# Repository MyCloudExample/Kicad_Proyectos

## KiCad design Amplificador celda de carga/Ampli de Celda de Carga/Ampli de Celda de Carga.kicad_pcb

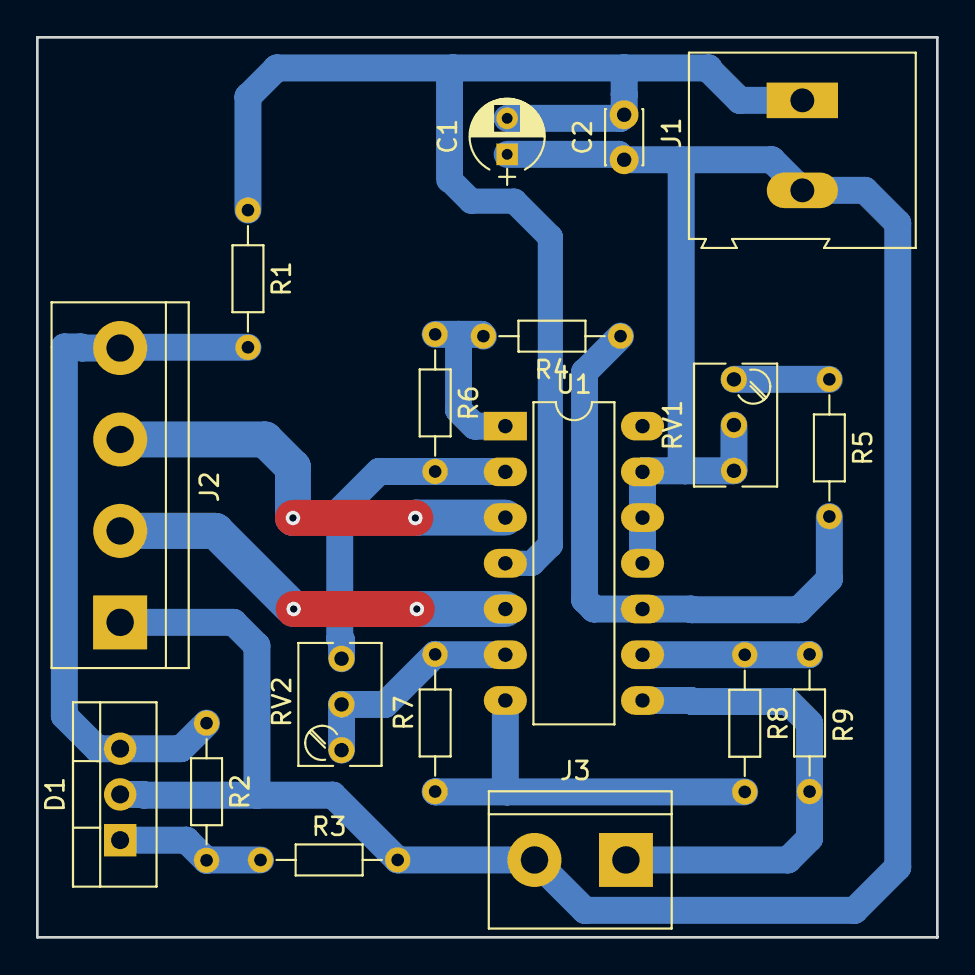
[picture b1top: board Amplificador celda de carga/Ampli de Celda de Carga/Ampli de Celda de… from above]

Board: 2 copper layers, 50.0 x 50.0 mm, 18 parts (0 on the bottom side), 14 nets.

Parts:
C1: 100uF; CP_Radial_D4.0mm_P2.00mm
C2: 0,1uF; C_Disc_D3.0mm_W2.0mm_P2.50mm
D1: TL431LP; TO-220-3_Vertical
J1: 12V GND; TerminalBlock_Altech_AK300-2_P5.00mm
J2: CargaBalanceada; TerminalBlock_bornier-4_P5.08mm
J3: Salida; TerminalBlock_bornier-2_P5.08mm
R1: 4k7; R_Axial_DIN0204_L3.6mm_D1.6mm_P7.62mm_Horizontal
R2, R3: 2k2; R_Axial_DIN0204_L3.6mm_D1.6mm_P7.62mm_Horizontal
R4, R6, R7, R8, R9: 10k; R_Axial_DIN0204_L3.6mm_D1.6mm_P7.62mm_Horizontal
R5: 8k2; R_Axial_DIN0204_L3.6mm_D1.6mm_P7.62mm_Horizontal
RV1: 2k; Potentiometer_Trimmer_Bourns_3266Y
RV2: 10k; Potentiometer_Trimmer_Bourns_3266Y
U1: LM324; DIP-14_W7.62mm_LongPads

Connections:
/5V: D1.3, J2.4, R1.2, R2.1
GNDREF: C1.1, C2.1, D1.2, J1.2, J2.1, J3.2, R3.2, RV1.2, RV1.3, U1.11, U1.12, U1.13
unnamed: D1.1, R2.2, R3.1
unnamed: J2.2, U1.5
unnamed: J2.3, U1.3
unnamed: J3.1, R9.1, U1.8
unnamed: R4.1, R5.2, U1.10
unnamed: R4.2, R6.1, U1.1
unnamed: R5.1, RV1.1
unnamed: R6.2, RV2.3, U1.2
unnamed: R7.1, R8.2, U1.7
unnamed: R7.2, RV2.1, RV2.2, U1.6
unnamed: R8.1, R9.2, U1.9
VDD: C1.2, C2.2, J1.1, R1.1, U1.4

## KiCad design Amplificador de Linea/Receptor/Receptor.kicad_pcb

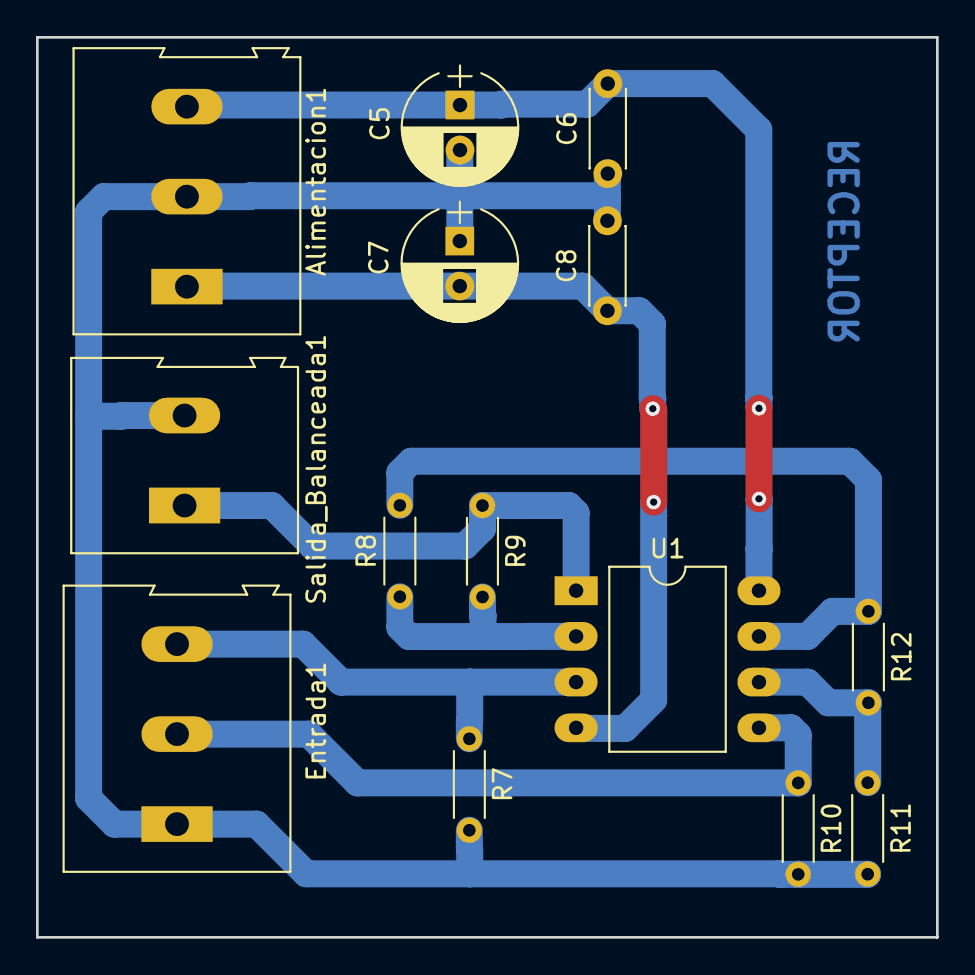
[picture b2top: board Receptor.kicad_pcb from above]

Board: 2 copper layers, 50.0 x 50.0 mm, 14 parts (0 on the bottom side), 9 nets.

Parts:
Alimentacion1: -12V 0V +12V; TerminalBlock_Altech_AK300-3_P5.00mm
C5, C7: 100uF; CP_Radial_D6.3mm_P2.50mm
C6, C8: 0,1uF; C_Disc_D4.3mm_W1.9mm_P5.00mm
Entrada1: TerminalBlock_Altech_AK300-3_P5.00mm
R7, R8, R9, R10, R11, R12: 10k; R_Axial_DIN0204_L3.6mm_D1.6mm_P5.08mm_Horizontal
Salida_Balanceada1: TerminalBlock_Altech_AK300-2_P5.00mm
U1: RC4558; DIP-8_W10.16mm_LongPads

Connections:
GNDREF: Alimentacion1.2, C5.2, C6.1, C7.1, C8.2, Entrada1.1, R7.2, R10.2, R11.2, Salida_Balanceada1.2
unnamed: Entrada1.2, R10.1, U1.5
unnamed: Entrada1.3, R7.1, U1.3
unnamed: R8.1, R9.2, U1.2
unnamed: R9.1, Salida_Balanceada1.1, U1.1
unnamed: R11.1, R12.2, U1.6
unnamed: R8.2, R12.1, U1.7
VDD: Alimentacion1.3, C5.1, C6.2, U1.8
VSS: Alimentacion1.1, C7.2, C8.1, U1.4

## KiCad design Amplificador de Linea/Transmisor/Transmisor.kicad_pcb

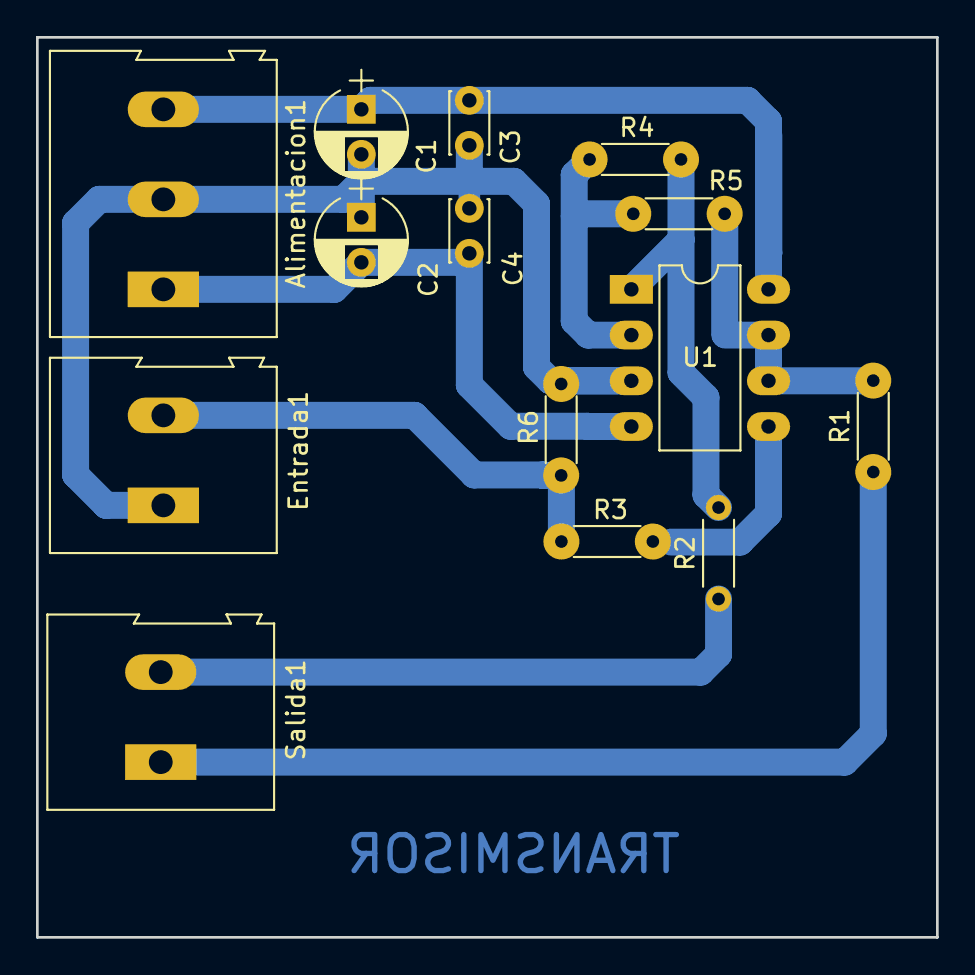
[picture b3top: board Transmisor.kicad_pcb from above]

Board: 2 copper layers, 50.0 x 50.0 mm, 14 parts (0 on the bottom side), 10 nets.

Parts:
Alimentacion1: -12V 0V +12V; TerminalBlock_Altech_AK300-3_P5.00mm
C1, C2: 100uF; CP_Radial_D5.0mm_P2.50mm
C3, C4: 0,1uF; C_Disc_D3.4mm_W2.1mm_P2.50mm
Entrada1: TerminalBlock_Altech_AK300-2_P5.00mm
R1, R2: 100; R_Axial_DIN0204_L3.6mm_D1.6mm_P5.08mm_Horizontal
R3: 1k; R_Axial_DIN0204_L3.6mm_D1.6mm_P5.08mm_Horizontal
R4, R5, R6: 10k; R_Axial_DIN0204_L3.6mm_D1.6mm_P5.08mm_Horizontal
Salida1: TerminalBlock_Altech_AK300-2_P5.00mm
U1: RC4558; DIP-8_W7.62mm_LongPads

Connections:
GNDREF: Alimentacion1.2, C1.2, C2.1, C3.1, C4.2, Entrada1.1, R6.1, U1.3
unnamed: Entrada1.2, R3.2, R6.2
unnamed: R1.1, Salida1.1
unnamed: R1.2, R4.2, U1.6, U1.7
unnamed: R2.1, Salida1.2
unnamed: R2.2, R5.1, U1.1
unnamed: R3.1, U1.5
unnamed: R4.1, R5.2, U1.2
VDD: Alimentacion1.3, C1.1, C3.2, U1.8
VSS: Alimentacion1.1, C2.2, C4.1, U1.4

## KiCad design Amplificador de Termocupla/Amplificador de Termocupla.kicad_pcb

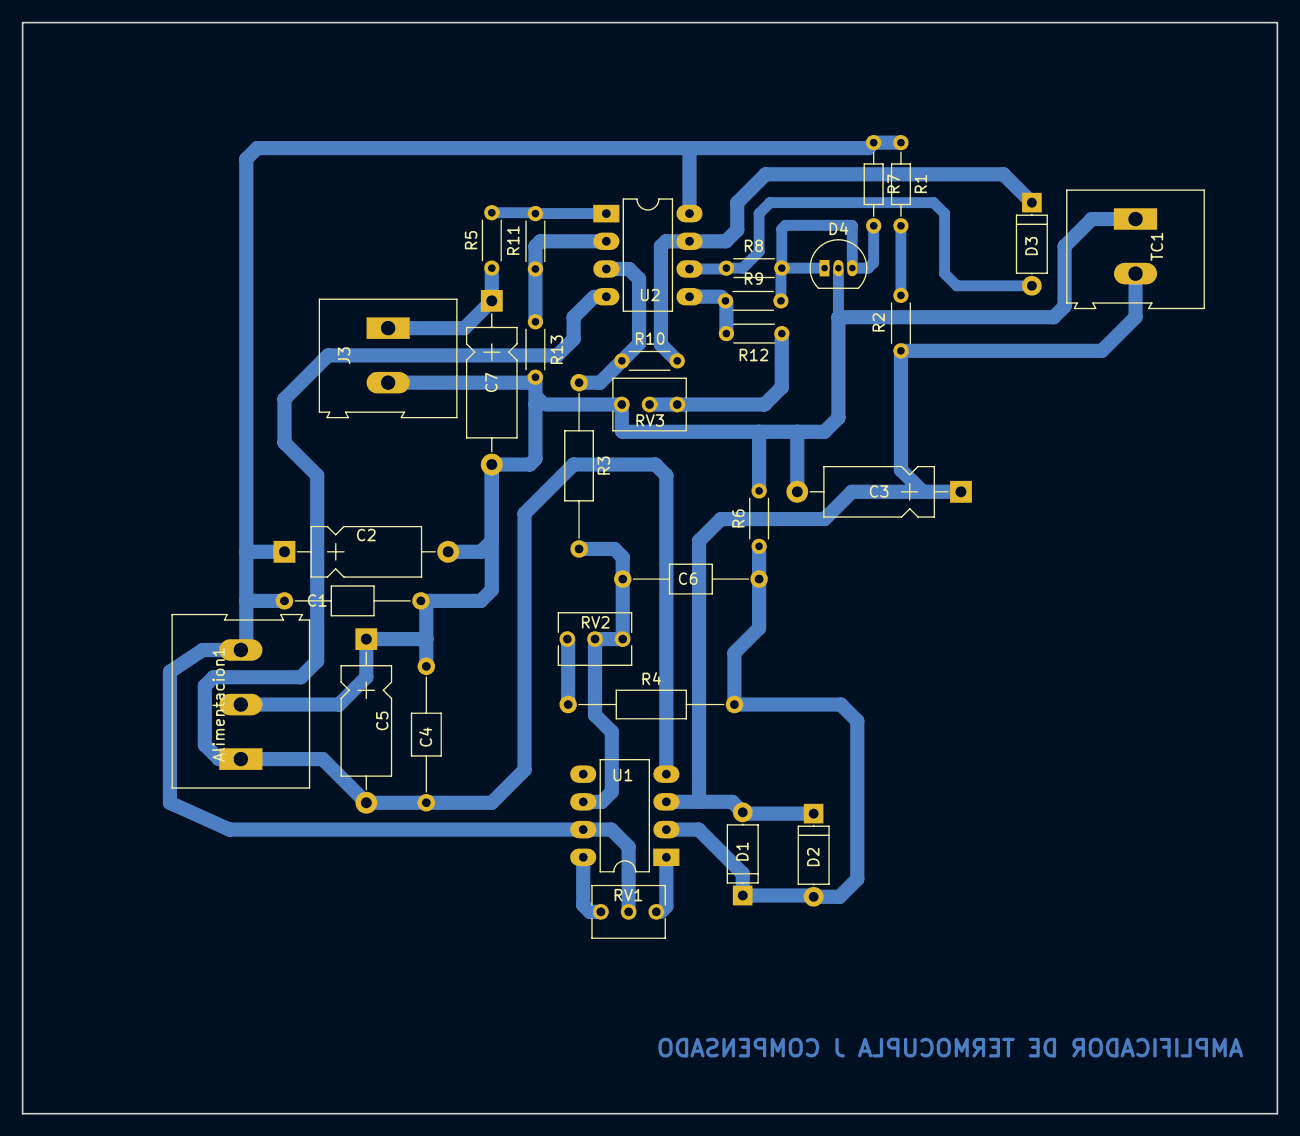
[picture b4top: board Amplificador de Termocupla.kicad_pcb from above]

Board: 2 copper layers, 115.0 x 100.0 mm, 32 parts (0 on the bottom side), 19 nets.

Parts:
Alimentacion1: -15 GND +15; TerminalBlock_Altech_AK300-3_P5.00mm
C1, C4, C6: 0.1uF; C_Axial_L3.8mm_D2.6mm_P12.50mm_Horizontal
C2, C5: 100uF; CP_Axial_L10.0mm_D4.5mm_P15.00mm_Horizontal
C3, C7: 1uF; CP_Axial_L10.0mm_D4.5mm_P15.00mm_Horizontal
D1, D2, D3: D_A-405_P7.62mm_Horizontal
D4: TL431LP; TO-92_Inline_Narrow_Oval
J3: Sensor_V_Out; TerminalBlock_Altech_AK300-2_P5.00mm
R1: 1M; R_Axial_DIN0204_L3.6mm_D1.6mm_P7.62mm_Horizontal
R2, R5, R6: 1K; R_Axial_DIN0204_L3.6mm_D1.6mm_P5.08mm_Horizontal
R3: 10K; R_Axial_DIN0207_L6.3mm_D2.5mm_P15.24mm_Horizontal
R4: 39K; R_Axial_DIN0207_L6.3mm_D2.5mm_P15.24mm_Horizontal
R7: R; R_Axial_DIN0204_L3.6mm_D1.6mm_P7.62mm_Horizontal
R8, R9: 18K; R_Axial_DIN0204_L3.6mm_D1.6mm_P5.08mm_Horizontal
R10, R13: 10K; R_Axial_DIN0204_L3.6mm_D1.6mm_P5.08mm_Horizontal
R11: 75K; R_Axial_DIN0204_L3.6mm_D1.6mm_P5.08mm_Horizontal
R12: 4K7; R_Axial_DIN0204_L3.6mm_D1.6mm_P5.08mm_Horizontal
RV1: 20K; Potentiometer_Trimmer_Vishay_T73XW_Vertical
RV2: 10K; Potentiometer_Trimmer_Vishay_T73XW_Vertical
RV3: 1K; Potentiometer_Trimmer_Vishay_T73XW_Vertical
TC1: Termocupla J; TerminalBlock_Altech_AK300-2_P5.00mm
U1: OP07; DIP-8_W7.62mm_LongPads
U2: LM358; DIP-8_W7.62mm_LongPads

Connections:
Earth: Alimentacion1.2, C1.2, C2.2, C3.2, C4.1, C5.1, C7.2, D4.2, J3.2, R6.2, R13.1, RV3.3, TC1.1
unnamed: C3.1, D1.2, D2.1, R2.2, TC1.2, U1.3
unnamed: C6.1, R3.2, RV2.1, RV2.2, U1.6
unnamed: C6.2, D1.1, D2.2, R4.2, R6.1, U1.2
unnamed: C7.1, J3.1, R5.1
unnamed: D3.1, R10.1, U2.7
unnamed: D3.2, R8.1, U2.6
unnamed: D4.1, D4.3, R7.2, R8.2, R9.1
unnamed: R1.2, R2.1
unnamed: R4.1, RV2.3
unnamed: R3.1, R10.2, U2.3
unnamed: R5.2, R11.1, U2.1
unnamed: R11.2, R13.2, U2.2
unnamed: R9.2, R12.1, U2.5
unnamed: R12.2, RV3.1, RV3.2
unnamed: RV1.1, U1.8
unnamed: RV1.3, U1.1
VDD: Alimentacion1.3, C1.1, C2.1, R1.1, R7.1, RV1.2, U1.7, U2.8
VEE: Alimentacion1.1, C4.2, C5.2, U1.4, U2.4

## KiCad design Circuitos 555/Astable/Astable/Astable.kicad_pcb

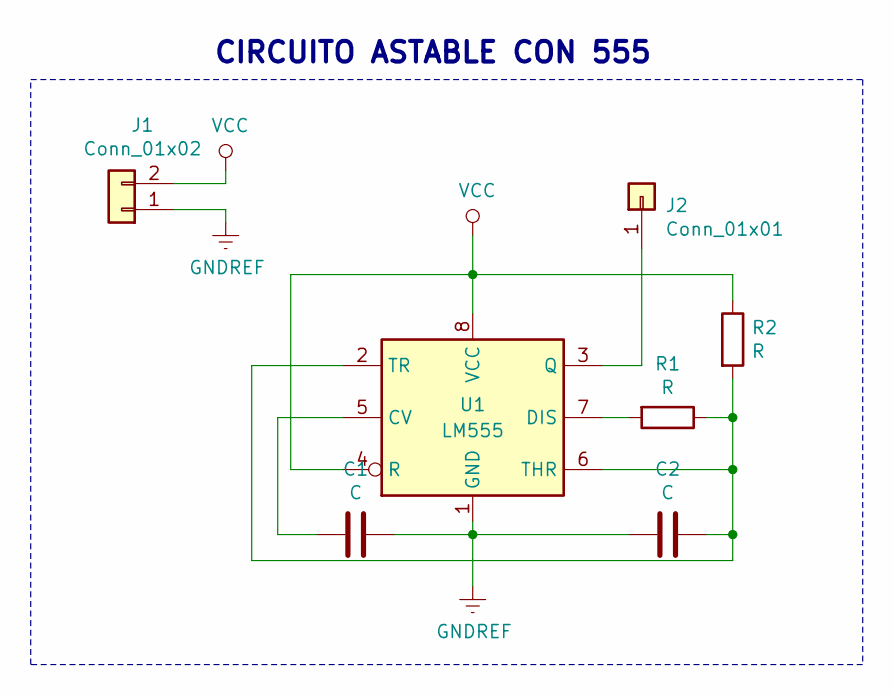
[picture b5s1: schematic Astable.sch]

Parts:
C1, C2: C; C_Axial_L3.8mm_D2.6mm_P7.50mm_Horizontal
J1: Conn_01x02; Molex_KK-6410-02_02x2.54mm_Straight
J2: Conn_01x01; 1pin
R1, R2: R; R_Axial_DIN0204_L3.6mm_D1.6mm_P7.62mm_Horizontal
U1: LM555; DIP-8_W7.62mm_LongPads

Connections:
GNDREF: C1.1, C2.2, J1.1, U1.1 (GND)
unnamed: C1.2, U1.5 (CV)
unnamed: C2.1, R1.1, R2.2, U1.2 (TR), U1.6 (THR)
unnamed: J2.1, U1.3 (Q)
unnamed: R1.2, U1.7 (DIS)
VCC: J1.2, R2.1, U1.4 (R), U1.8 (VCC)

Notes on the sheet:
CIRCUITO ASTABLE CON 555

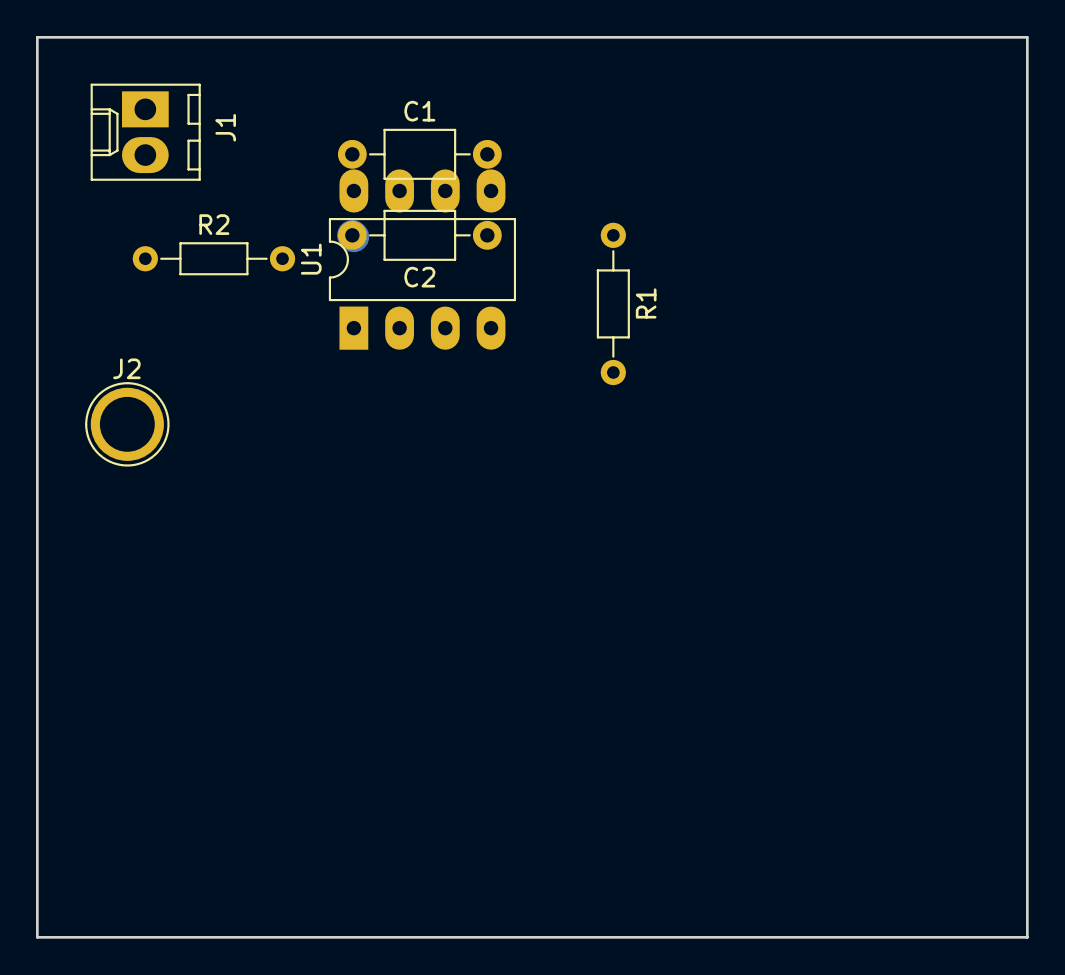
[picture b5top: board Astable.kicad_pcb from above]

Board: 2 copper layers, 55.0 x 50.0 mm, 7 parts (0 on the bottom side), 6 nets.

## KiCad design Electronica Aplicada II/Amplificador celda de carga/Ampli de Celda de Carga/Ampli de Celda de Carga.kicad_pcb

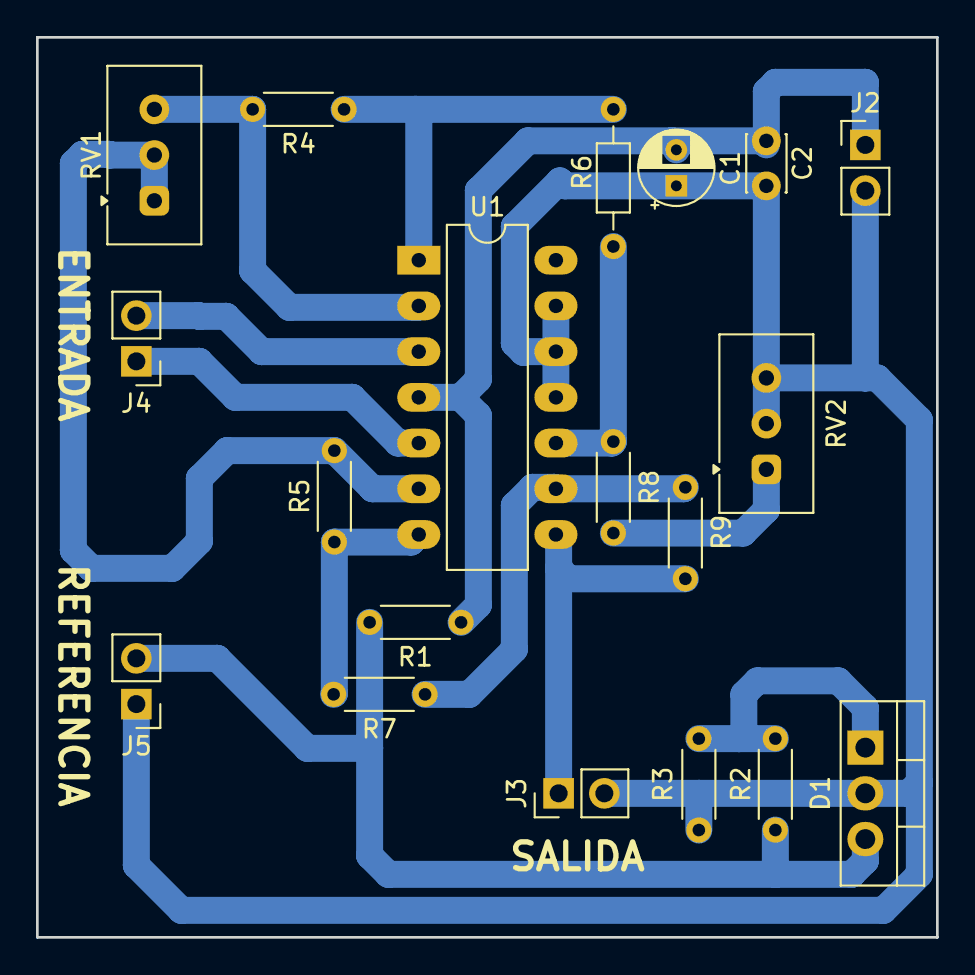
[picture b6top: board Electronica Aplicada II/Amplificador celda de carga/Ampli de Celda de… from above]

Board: 2 copper layers, 50.0 x 50.0 mm, 19 parts (0 on the bottom side), 14 nets.

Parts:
C1: C_Polarized; CP_Radial_D4.0mm_P2.00mm
C2: 0,1uF; C_Disc_D3.0mm_W2.0mm_P2.50mm
D1: TL431LP; TO-220-3_Vertical
J2: 12V GND; PinHeader_1x02_P2.54mm_Vertical
J3: Salida; PinHeader_1x02_P2.54mm_Vertical
J4: ENTRADA; PinHeader_1x02_P2.54mm_Vertical
J5: REFERENCIA; PinHeader_1x02_P2.54mm_Vertical
R1: 4k7; R_Axial_DIN0204_L3.6mm_D1.6mm_P5.08mm_Horizontal
R2, R3: 2k2; R_Axial_DIN0204_L3.6mm_D1.6mm_P5.08mm_Horizontal
R4, R5, R7, R9: 10k; R_Axial_DIN0204_L3.6mm_D1.6mm_P5.08mm_Horizontal
R6: 10k; R_Axial_DIN0204_L3.6mm_D1.6mm_P7.62mm_Horizontal
R8: 8k2; R_Axial_DIN0204_L3.6mm_D1.6mm_P5.08mm_Horizontal
RV1, RV2: R_Potentiometer; Potentiometer_Vishay_T93YA_Vertical
U1: LM324; CERDIP-14_W7.62mm_SideBrazed_LongPads

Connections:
/5V: D1.3 (K), J5.2, R1.2, R2.1
GND: C1.1, C2.1, D1.2 (A), J2.2, J3.2, J5.1, R3.2, RV2.2, RV2.3, U1.11 (V-), U1.12 (+), U1.13 (-)
unnamed: D1.1 (REF), R2.2, R3.1
unnamed: J3.1, R9.1, U1.8
unnamed: J4.1, U1.5 (+)
unnamed: J4.2, U1.3 (+)
unnamed: R4.1, R6.2, U1.1
unnamed: R5.1, R7.2, U1.7
unnamed: R8.1, RV2.1
unnamed: R4.2, RV1.3, U1.2 (-)
unnamed: R5.2, RV1.1, RV1.2, U1.6 (-)
unnamed: R6.1, R8.2, U1.10 (+)
unnamed: R7.1, R9.2, U1.9 (-)
VDD: C1.2, C2.2, J2.1, R1.1, U1.4 (V+)
